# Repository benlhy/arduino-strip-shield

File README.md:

# Arduino Strip Shield
Schematics for a LED strip driver Arduino shield. Good for up to 1A! Can be used with 12V light strips, 12V RGB strips, and 5V neopixel strips.

WARNING: If you want to use the power from the VIN pin to power your neopixel strip, you will need a step-down voltage regulator from 12V to 5V before connecting your neopixel strip because the PWR pin supplies power directly from the DC jack. Connecting a 5V power supply to the DC jack will NOT work because it needs 7-12V to feed into the Arduino.

Remember to disconnect DC power when connecting the programming header just to be safe.

Use RTClib to use the RTC, and Radiohead to use the NRF24L01

D3: Power (PWM)
D4: Neopixel
D5: Red
D6: Green
D9: Blue

# To test
* Connect 5V DC power and USB power. Board should be powered.
* Jump VIN to 5V if 5V DC supply, and cut the VIN connection. Board should be powered.

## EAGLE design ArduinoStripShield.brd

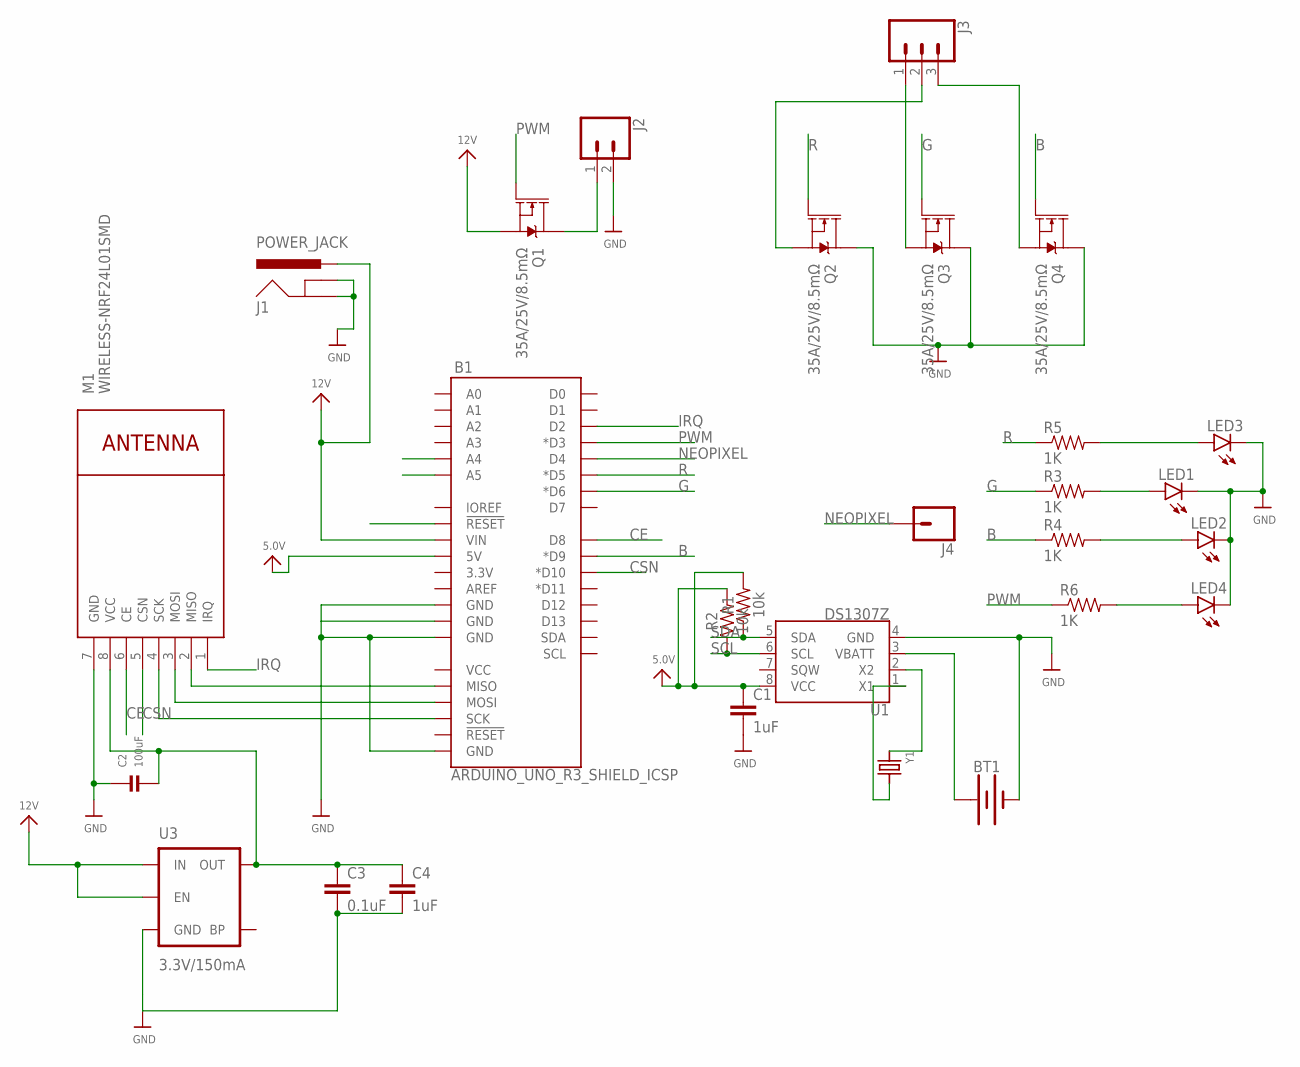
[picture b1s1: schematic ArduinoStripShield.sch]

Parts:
B1: ARDUINO_UNO_R3_SHIELD_ICSP; UNO_R3_SHIELD_ICSP
BT1: BATTERY-12MM_SMD; BATTCON_12MM
C1, C4: 1uF; 0805
C2: 100uF; 1206
C3: 0.1uF; 0805
J1: POWER_JACK; POWER_JACK_PTH
J2: CONN_02; 1X02
J3: CONN_03; 1X03
J4: CONN_01; 1X01
LED1, LED2, LED3, LED4: LED0603; LED-0603
M1: WIRELESS-NRF24L01SMD; WIRELESS-NRF24L01-SMD
Q1, Q2, Q3, Q4: 35A/25V/8.5mΩ; DPAK
R1, R2: 10k; 0603
R3, R4, R5, R6: 1K; 0603-RES
U1: DS1307Z; SO08-0.15
U3: 3.3V/150mA; SOT23-5
Y1: CRYSTAL8X3.8SMT; CRYSTAL_8X3.8

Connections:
5.0V: B1.5V, C1.1, R1.2, R2.2, U1.8 (VCC)
12V: B1.VIN, J1.PWR, Q1.3 (S), U3.1 (IN), U3.3 (EN)
B: B1.D9 (*D9), Q4.1 (G), R4.1
CE: B1.D8, M1.6 (CE)
CSN: B1.D10 (*D10), M1.5 (CSN)
G: B1.D6 (*D6), Q3.1 (G), R3.1
GND: B1.GND@0 (GND), B1.GND@1 (GND), B1.GND@2 (GND), B1.GND_ICSP (GND), BT1.GND (-), C1.2, C2.1, C3.2, C4.2, J1.GND, J1.GNDBREAK, J2.2, LED1.C, LED2.C, LED3.C, LED4.C, M1.7 (GND), Q2.4 (D), Q3.4 (D), Q4.4 (D), U1.4 (GND), U3.2 (GND)
IRQ: B1.D2, M1.1 (IRQ)
unnamed: J2.1, Q1.4 (D)
unnamed: B1.MISO, M1.2 (MISO)
unnamed: B1.MOSI, M1.3 (MOSI)
unnamed: J3.1, Q3.3 (S)
unnamed: J3.2, Q2.3 (S)
unnamed: J3.3, Q4.3 (S)
unnamed: BT1.PWR@1 (+), U1.3 (VBATT)
unnamed: U1.2 (X2), Y1.P$1 (1)
unnamed: U1.1 (X1), Y1.P$4 (2)
unnamed: B1.SCK, M1.4 (SCK)
unnamed: C2.2, C3.1, C4.1, M1.8 (VCC), U3.5 (OUT)
unnamed: LED2.A, R4.2
unnamed: LED4.A, R6.2
unnamed: LED3.A, R5.2
unnamed: LED1.A, R3.2
NEOPIXEL: B1.D4, J4.1
PWM: B1.D3 (*D3), Q1.1 (G), R6.1
R: B1.D5 (*D5), Q2.1 (G), R5.1
RST: B1.RES (!RESET!)
SCL: B1.A5, R2.1, U1.6 (SCL)
SDA: B1.A4, R1.1, U1.5 (SDA)

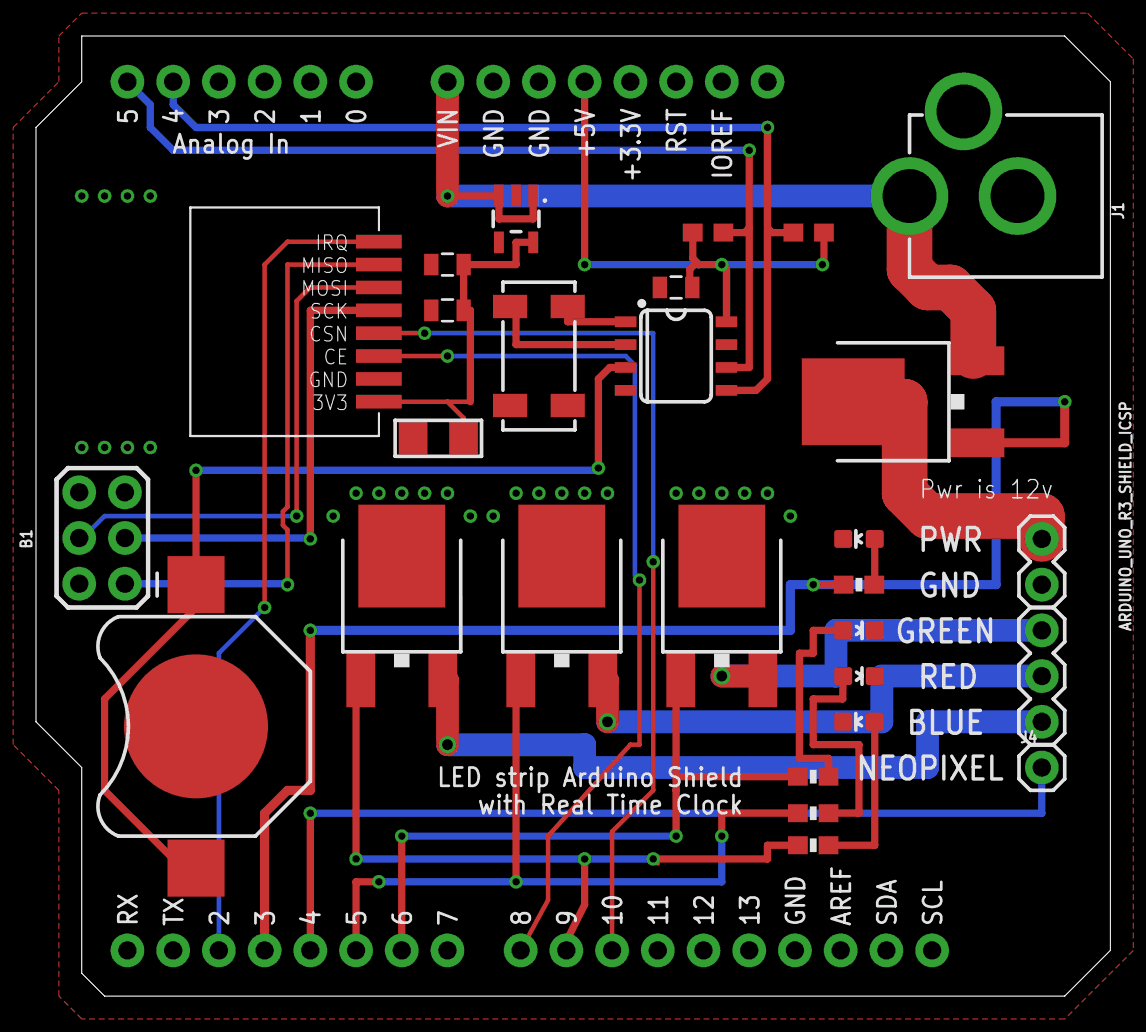
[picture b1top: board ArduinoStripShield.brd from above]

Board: 2 copper layers, 59.7 x 53.3 mm, 28 parts (0 on the bottom side), 28 nets.

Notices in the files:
parts and their libraries:
SparkFun-Boards: Licensing: Creative Commons ShareAlike 4.0 International - https://creativecommons.org/licenses/by-sa/4.0
microbuilder: This work is placed in the public domain, and may be freely used for commercial and non-commercial work with the following conditions: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
